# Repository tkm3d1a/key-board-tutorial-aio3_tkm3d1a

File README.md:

# key-board-tutorial-aio3_tkm3d1a
 My first testing using Kicad and building sample layouts

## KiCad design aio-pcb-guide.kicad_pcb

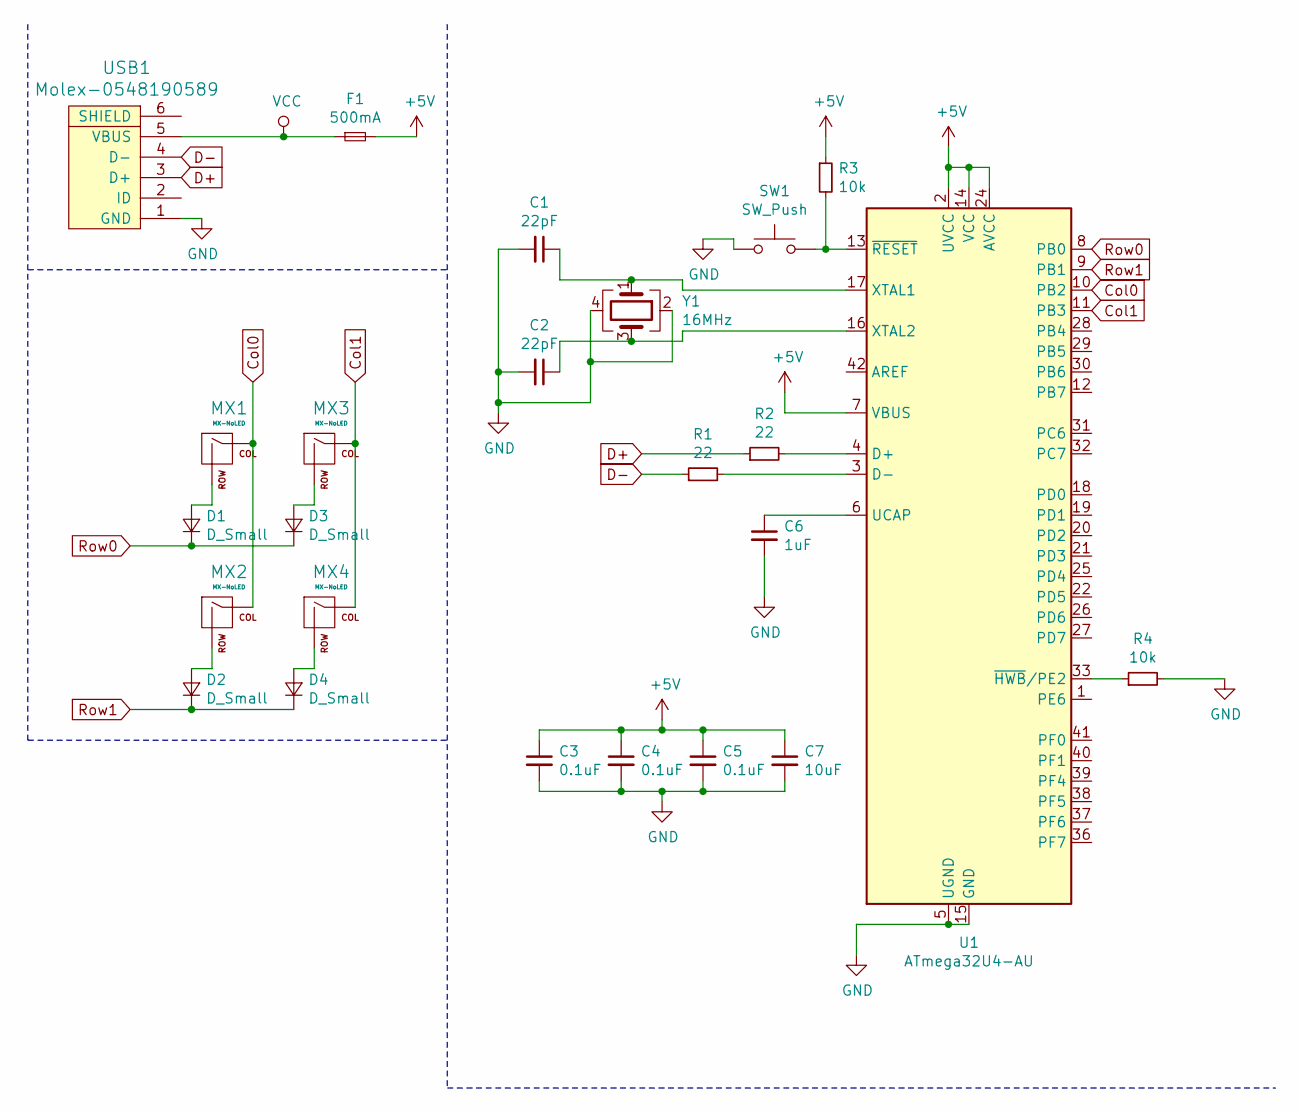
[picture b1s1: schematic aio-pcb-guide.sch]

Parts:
C1, C2: 22pF; C_0805_2012Metric
C3, C4, C5: 0.1uF; C_0805_2012Metric
C6: 1uF; C_0805_2012Metric
C7: 10uF; C_0805_2012Metric
D1, D2, D3, D4: D_Small; D_SOD-123
F1: 500mA; Fuse_1206_3216Metric
MX1, MX2, MX3, MX4: MX-NoLED; MXOnly-1U-NoLED
R1, R2: 22; R_0805_2012Metric
R3, R4: 10k; R_0805_2012Metric
SW1: SW_Push; SKQG-1155865
U1: ATmega32U4-AU; TQFP-44_10x10mm_P0.8mm
USB1: Molex-0548190589
Y1: 16MHz; Crystal_SMD_3225-4Pin_3.2x2.5mm

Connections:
+5V: C3.1, C4.1, C5.1, C7.1, F1.2, R3.1, U1.2 (UVCC), U1.7 (VBUS), U1.14 (VCC), U1.24 (AVCC), U1.34 (VCC), U1.44 (AVCC)
Col0: MX1.1 (COL), MX2.1 (COL), U1.10 (PB2)
Col1: MX3.1 (COL), MX4.1 (COL), U1.11 (PB3)
D+: R2.1, USB1.3 (D+)
D-: R1.1, USB1.4 (D-)
GND: C1.2, C2.2, C3.2, C4.2, C5.2, C6.2, C7.2, R4.2, SW1.1, U1.5 (UGND), U1.15 (GND), U1.23 (GND), U1.35 (GND), U1.43 (GND), USB1.1 (GND), Y1.2, Y1.4
unnamed: C1.1, U1.17 (XTAL1), Y1.1
unnamed: C2.1, U1.16 (XTAL2), Y1.3
unnamed: C6.1, U1.6 (UCAP)
unnamed: D1.2 (A), MX1.2 (ROW)
unnamed: D2.2 (A), MX2.2 (ROW)
unnamed: D3.2 (A), MX3.2 (ROW)
unnamed: D4.2 (A), MX4.2 (ROW)
unnamed: R1.2, U1.3 (D-)
unnamed: R2.2, U1.4 (D+)
unnamed: R3.2, SW1.2, U1.13 (~RESET)
unnamed: R4.1, U1.33 (~HWB~/PE2)
Row0: D1.1 (K), D3.1 (K), U1.8 (PB0)
Row1: D2.1 (K), D4.1 (K), U1.9 (PB1)
VCC: F1.1, USB1.5 (VBUS)

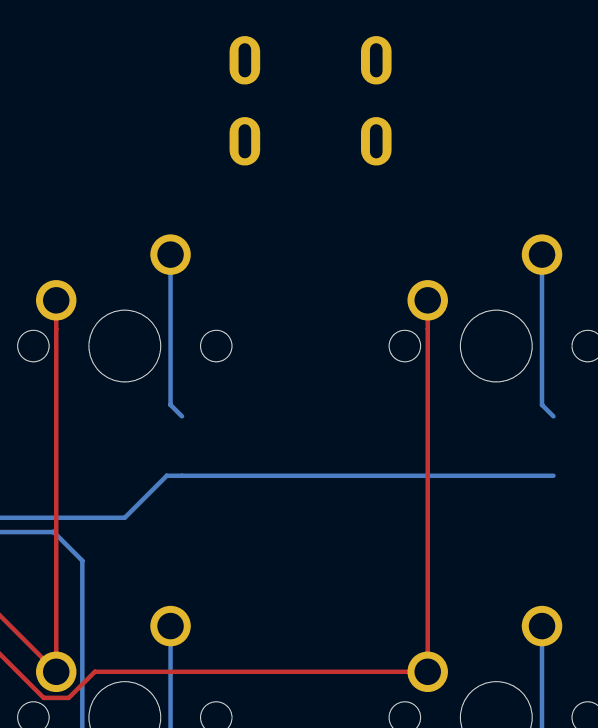
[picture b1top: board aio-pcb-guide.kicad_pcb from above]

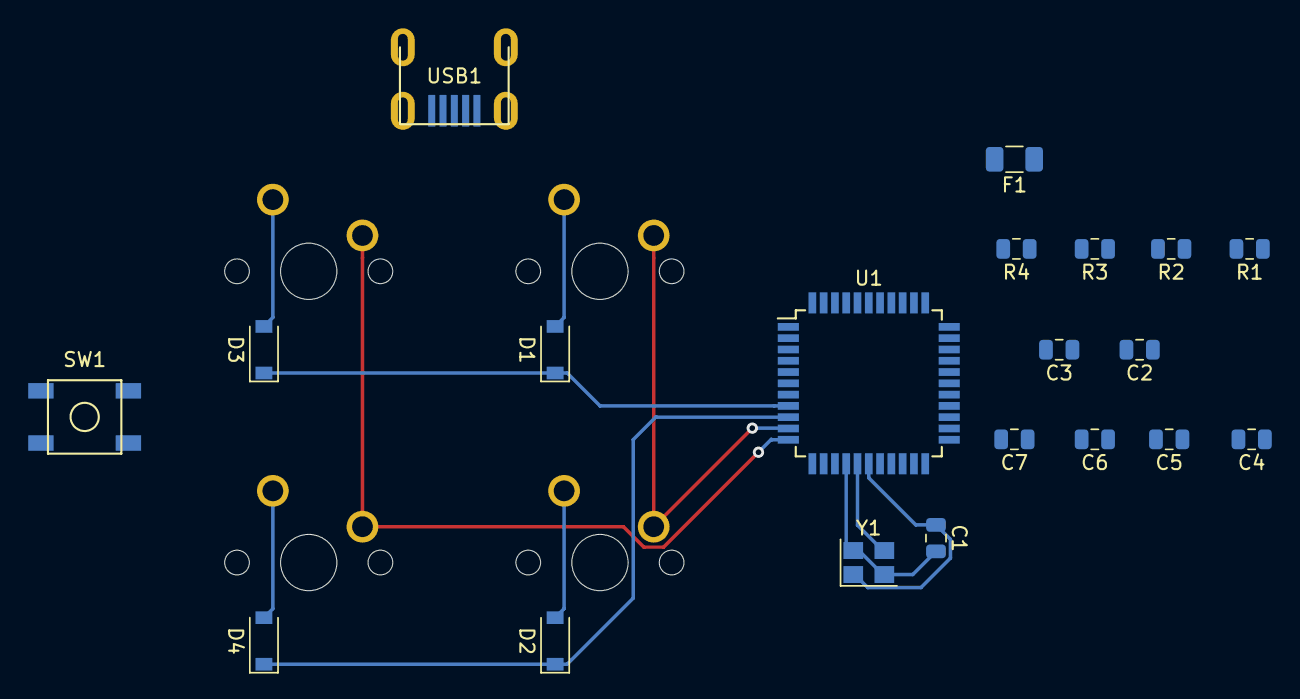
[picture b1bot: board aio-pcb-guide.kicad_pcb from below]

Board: 2 copper layers, 24 parts (20 on the bottom side), 20 nets.

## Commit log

2020-12-18 Project Init
    project init_empty files
2020-12-19 Add Submodules
2020-12-19 Added schema and footprint libraries
2020-12-19 deleted extra folder
2020-12-19 Schematic started - v01
2020-12-19 completed MCU
2020-12-19 Footprints applied
2020-12-19 PCB Started v01
2020-12-20 Some Routing Completed
2021-01-05 removed at32u4 datasheet
